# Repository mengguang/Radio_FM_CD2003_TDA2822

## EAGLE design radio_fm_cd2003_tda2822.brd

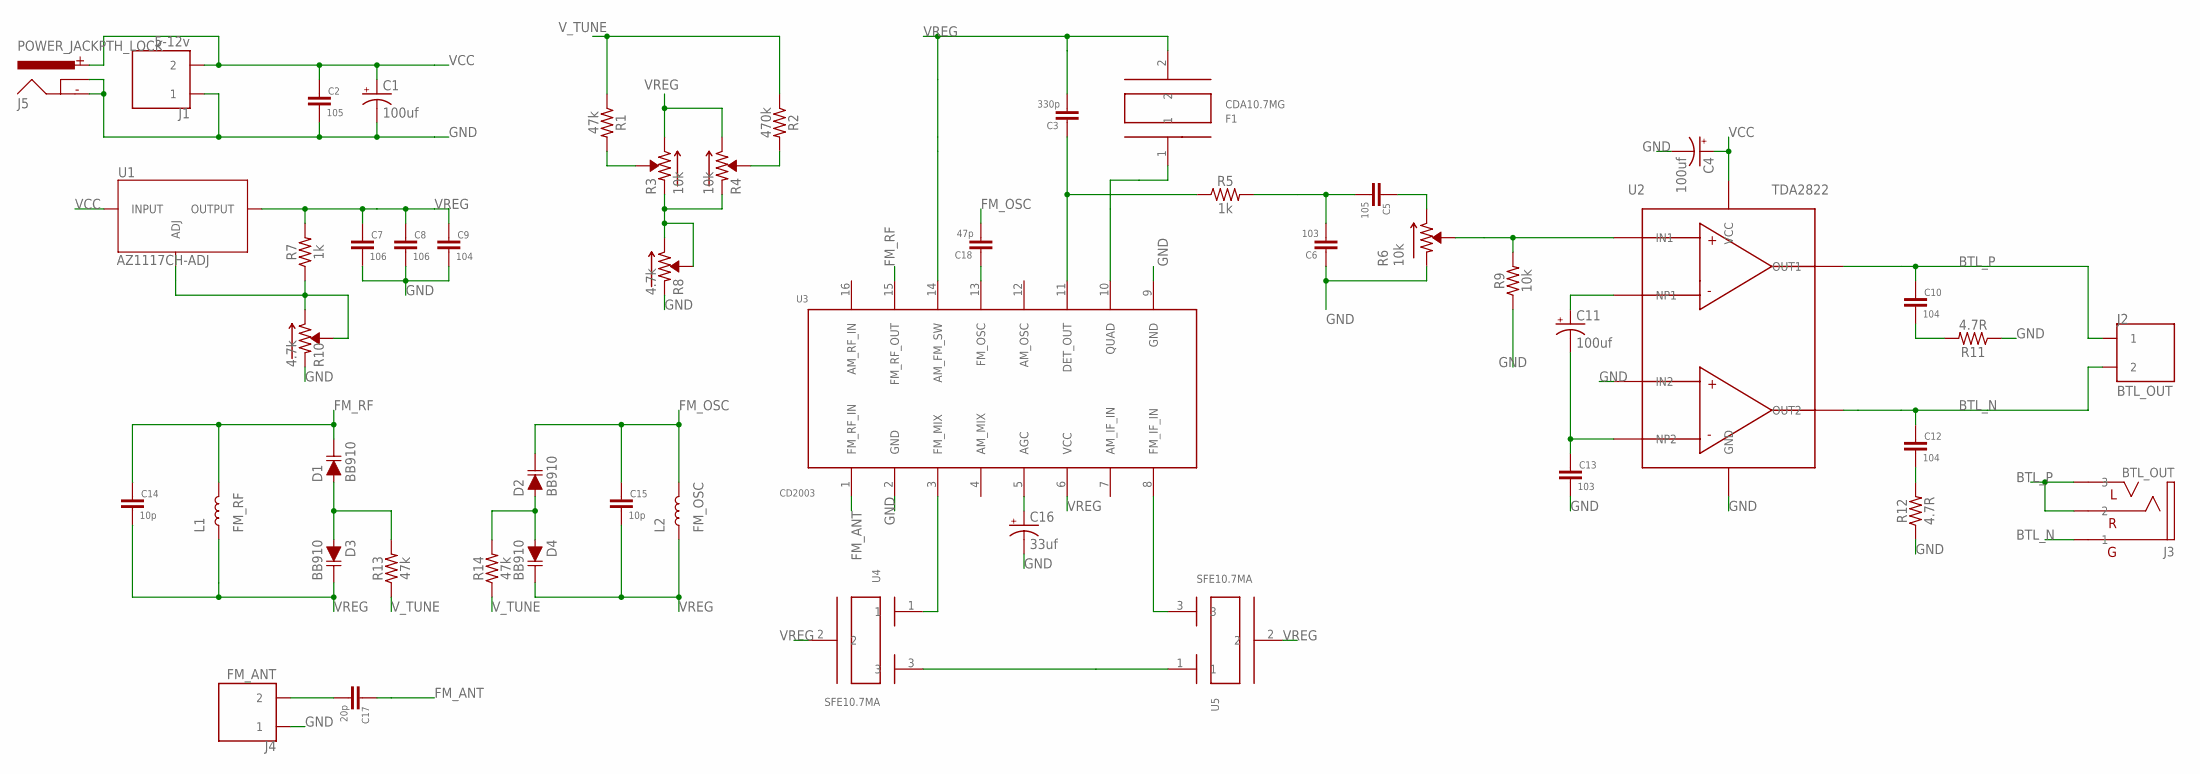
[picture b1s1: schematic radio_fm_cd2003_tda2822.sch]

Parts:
C1, C4, C11: 100uf; CAP_2.5MM
C2, C5: 105; C0603
C3: 330p; C0603
C6, C13: 103; C0603
C7, C8: 106; C0603
C9, C10, C12: 104; C0603
C14, C15: 10p; C0603
C16: 33uf; CAP_2MM
C17: 20p; C0603
C18: 47p; C0603
D1, D2, D3, D4: BB910; TO-92S
F1: CDA10.7MG
J1: 5-12v; 2P_2.54MM
J2: BTL_OUT; 2P_5.08MM
J3: BTL_OUT; 3.5MM
J4: FM_ANT; 2P_2.54MM
J5: POWER_JACKPTH_LOCK; POWER_JACK_PTH_LOCK
L1: FM_RF; VLU0810
L2: FM_OSC; VLU0810
R1, R13, R14: 47k; R0603
R2: 470k; R0603
R3, R4, R6: 10k; 3362P
R5, R7: 1k; R0603
R8, R10: 4.7k; 3362P
R9: 10k; R0603
R11, R12: 4.7R; R0603
U1: AZ1117CH-ADJ; SOT-223
U2: TDA2822; DIP8
U3: CD2003; DIP16
U4, U5: SFE10.7MA

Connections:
BTL_N: C12.1, J2.N (2), J3.P$1 (1), U2.P$3 (OUT2)
BTL_P: C10.1, J2.L (1), J3.P$2 (2), J3.P$3 (3), U2.P$1 (OUT1)
FM_ANT: C17.1, U3.1 (FM_RF_IN)
FM_OSC: C15.1, C18.2, D2.2 (C), L2.- (2)
FM_RF: C14.1, D1.2 (C), L1.- (2), U3.15 (FM_RF_OUT)
GND: C1.-, C2.2, C4.-, C6.1, C7.2, C8.2, C9.2, C13.2, C16.-, J1.1, J4.1, J5.GND, J5.GNDBREAK, R6.P$1 (1), R8.P$1 (1), R9.1, R10.P$1 (1), R11.1, R12.1, U2.P$4 (GND), U2.P$6 (IN2), U3.2 (GND), U3.9 (GND)
unnamed: C11.+, U2.P$8 (NP1)
unnamed: C12.2, R12.2
unnamed: C11.-, C13.1, U2.P$5 (NP2)
unnamed: C5.1, R6.P$3 (3)
unnamed: C3.1, R5.1, U3.11 (DET_OUT)
unnamed: D1.1 (A), D3.1 (A), R13.2
unnamed: C16.+, U3.5 (AGC)
unnamed: R7.1, R10.P$2 (2), R10.P$3 (3), U1.1 (ADJ)
unnamed: D2.1 (A), D4.1 (A), R14.2
unnamed: U3.3 (FM_MIX), U4.1
unnamed: U3.8 (FM_IF_IN), U5.3
unnamed: R1.2, R3.P$2 (2)
unnamed: U4.3, U5.1
unnamed: F1.1, U3.10 (QUAD)
unnamed: C10.2, R11.2
unnamed: C17.2, J4.2
unnamed: C5.2, C6.2, R5.2
unnamed: C18.1, U3.13 (FM_OSC)
unnamed: R3.P$1 (1), R4.P$1 (1), R8.P$2 (2), R8.P$3 (3)
unnamed: R6.P$2 (2), R9.2, U2.P$7 (IN1)
unnamed: R2.2, R4.P$2 (2)
VCC: C1.+, C2.1, C4.+, J1.2, J5.PWR, U1.3 (INPUT), U2.P$2 (VCC)
VREG: C3.2, C7.1, C8.1, C9.1, C14.2, C15.2, D3.2 (C), D4.2 (C), F1.2, L1.+ (1), L2.+ (1), R3.P$3 (3), R4.P$3 (3), R7.2, U1.2 (OUTPUT), U3.6 (VCC), U3.14 (AM_FM_SW), U4.2, U5.2
V_TUNE: R1.1, R2.1, R13.1, R14.1

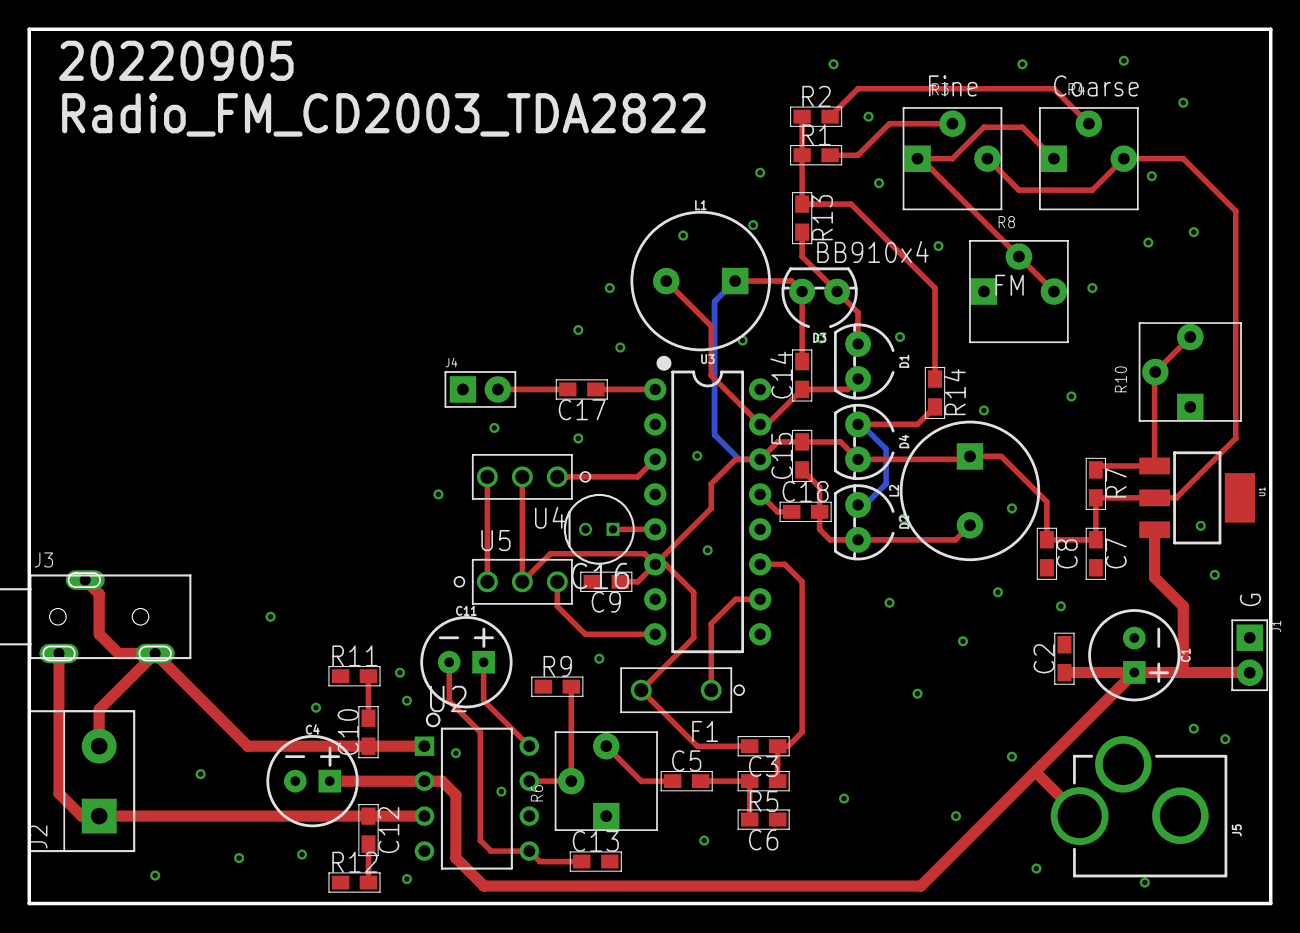
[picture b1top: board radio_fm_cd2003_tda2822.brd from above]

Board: 2 copper layers, 90.2 x 63.5 mm, 49 parts (0 on the bottom side), 30 nets.

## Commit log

2022-09-09 20220905
